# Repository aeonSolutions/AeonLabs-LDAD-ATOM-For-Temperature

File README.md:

[PCB-Prototyping-Catalogue](https://github.com/aeonSolutions/PCB-Prototyping-Catalogue)  >>  [Laboratory Automation](https://github.com/aeonSolutions/PCB-Prototyping-Catalogue/tree/main/Laboratory%20Automation) >>  [Smart DAQs](https://github.com/aeonSolutions/PCB-Prototyping-Catalogue/tree/main/Smart%20DAQ)  >>    [12-bit Smart DAQs](https://github.com/aeonSolutions/PCB-Prototyping-Catalogue/tree/main/Smart%20DAQ/12-bit)  >> LDAD ATOM For Temperature

<br>

#  LDAD ATOM For Temperature
This repo contains the KiCad files for the LDAD ATOM features 1 DS18b20 temperature sensor, has WIFI and BLE connectivity, externally powered 3.3V to 12V such as a USB plug.

LDAD ATOM features 1 I2C (or 1 digital in)  connection, has WIFI and BLE connectivity, externally powered 3.3V to 12V such as a USB plug. This PCB was made to Fit a 45x25mm enclosure.
It can connect 1 digital sensor and up to 8 I2C sensors.

This PCB was made to Fit a [45x25mm](https://s.click.aliexpress.com/e/_A5Elob) enclosure.

*Don't forget to LIKE , SHARE and subscribe the free whatsApp group* and if you liked this PCB consider buying me a cup of coffee. Links below.

### Status
  revision 1.0 tested and working.

If you already tested this PCB send me a message. Thank you

## Revisions
- revision 1.0
  
## Download options
Download this repository if you need the KiCad Files or, download the Gerber files in the release section of this repository

## Liked it ? Get a Free PCB for yourself
Send me your Device or hardware and i will design a custom PCB for it. Free of charge. Contact-me on WhatsApp or email for more info. 

## Q&A WhatsApp Group
If you have any Questions or simply  like this kind of projects and want to stay updated with the latest research ideas and prototypes during the day and week, join the WhatsApp Group
[A.I. Things](https://chat.whatsapp.com/FkNC7u83kuy2QRA5sqjBVg)

## Fully assembled PCB
Alternatively, and if you do not want to build a PCB by yourself and like to buy one:

The price starts at 30eur plus postage fees.
(I will also deliver the assembled PCB with all the components in place at a fair aditonal cost).

#### Be supportive of my dedication and work towards technology education and buy me a coffee. Link below.

________________________________________________________________________________________________________________
## [Go back to main catalogue page](https://github.com/aeonSolutions/PCB-Prototyping-Catalogue)
________________________________________________________________________________________________________________

## PCB Parts list
- DC2DC converter HX4002B x2 : https://s.click.aliexpress.com/e/_Ak7IPx
- Capacitor 100nF SMD 1206 : https://s.click.aliexpress.com/e/_AVdmzr
- Capacitor 2.2uF SMD 1206 : https://s.click.aliexpress.com/e/_AVdmzr
- Resistor SMD 1206 330R x3 : https://s.click.aliexpress.com/e/_A7OXrR
- ESP32 WROOM32 x1 : https://s.click.aliexpress.com/e/_AF7N6l
- KF350 Screw pitch 3.5mm Straight 4 Pin pcb terminal block : https://s.click.aliexpress.com/e/_AChDnp

- This PCB connects with the any I2C compatible sensor such as the SHT3x, SG30, etc :  https://s.click.aliexpress.com/e/_A1piJN

## PCB Enclosure
The enclosure,  a [45x25mm](https://s.click.aliexpress.com/e/_A5Elob) enclosure, for this PCB can be bought online on AliExpress.com

## Firmware Download 
one can use the PCB in the repository [AeonLabs-MCU-Burner-USB-to-UART-TTL](https://github.com/aeonSolutions/AeonLabs-MCU-Burner-USB-to-UART-TTL) to program the ESP32 WROOM32 MCU on this PCB.

______________________________________________________________________________________________________________________________

### License
2022 Creative Commons Attribution-NonCommercial-ShareAlike 4.0 International

https://creativecommons.org/licenses/by-nc-sa/4.0/

### Own a copy of this work
if you like to own a copy of this work, you can buy it as a NFT or Ethereum. contact me for more details at mtpsilva@gmail.com

=====================================================================================
### Share this PCB board files

### Be supportive of my dedication and work towards technology education and buy me a coffee

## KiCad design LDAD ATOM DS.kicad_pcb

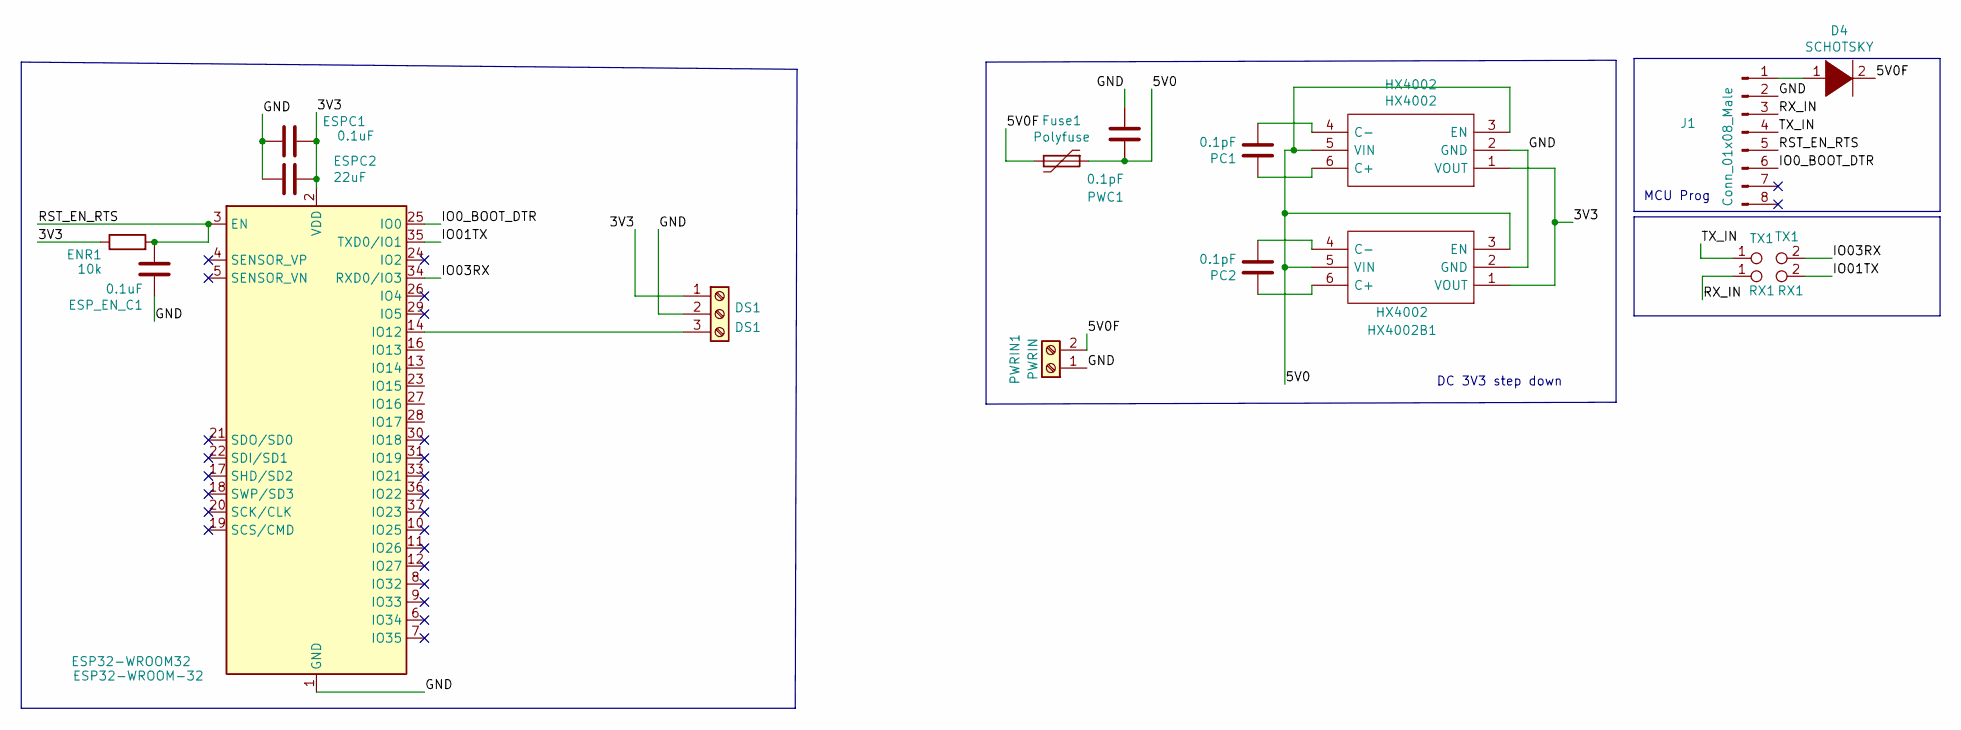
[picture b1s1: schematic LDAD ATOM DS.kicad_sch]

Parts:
D4: SCHOTSKY; D_1210_3225Metric_Pad1.42x2.65mm_HandSolder
DS1: DS1; TerminalBlock_4Ucon_1x03_P3.50mm_Vertical
ENR1: 10k; R_1206_3216Metric_Pad1.30x1.75mm_HandSolder
ESP32-WROOM32: ESP32-WROOM-32
ESPC1: 0.1uF; C_1206_3216Metric_Pad1.33x1.80mm_HandSolder
ESPC2: 22uF; C_1206_3216Metric_Pad1.33x1.80mm_HandSolder
ESP_EN_C1: 0.1uF; C_1206_3216Metric_Pad1.33x1.80mm_HandSolder
Fuse1: Polyfuse; Fuse_1206_3216Metric_Pad1.42x1.75mm_HandSolder
HX4002, HX4002B1: HX4002; HX4002 SOT95 P280X125-6N; Manufacturer_Part_Number HX4002
J1: Conn_01x08_Male; SOIC_clipProgSmall
PC1, PC2: 0.1pF; C_1206_3216Metric_Pad1.33x1.80mm_HandSolder
PWC1: 0.1pF; C_1206_3216Metric_Pad1.33x1.80mm_HandSolder
PWRIN1: PWRIN; TestPoint_2Pads_Pitch2.54mm_Drill0.8mm
RX1: RX1; TestPoint_Pad_Bridge_1.0x1.0mm
TX1: TX1; TestPoint_Pad_Bridge_1.0x1.0mm

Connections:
/3V3: DS1.1, ENR1.1, ESP32-WROOM32.2 (VDD), ESPC1.1, ESPC2.1, HX4002.1 (VOUT), HX4002B1.1 (VOUT)
/5V0: Fuse1.1, HX4002.3 (EN), HX4002.5 (VIN), HX4002B1.3 (EN), HX4002B1.5 (VIN), PWC1.1
/5V0F: D4.2 (A), Fuse1.2, PWRIN1.2
/GND: DS1.2, ESP32-WROOM32.1 (GND), ESP32-WROOM32.15 (GND), ESP32-WROOM32.38 (GND), ESP32-WROOM32.39 (GND), ESPC1.2, ESPC2.2, ESP_EN_C1.1, HX4002.2 (GND), HX4002B1.2 (GND), J1.2, PWC1.2, PWRIN1.1
/IO0_BOOT_DTR: ESP32-WROOM32.25 (IO0), J1.6
/IO01TX: ESP32-WROOM32.35 (TXD0/IO1), RX1.2
/IO03RX: ESP32-WROOM32.34 (RXD0/IO3), TX1.2
/RST_EN_RTS: ENR1.2, ESP32-WROOM32.3 (EN), ESP_EN_C1.2, J1.5
/RX_IN: J1.3, RX1.1
/TX_IN: J1.4, TX1.1
unnamed: DS1.3, ESP32-WROOM32.14 (IO12)
unnamed: HX4002.4 (C-), PC1.2
unnamed: HX4002.6 (C+), PC1.1
unnamed: HX4002B1.4 (C-), PC2.2
unnamed: HX4002B1.6 (C+), PC2.1
unnamed: D4.1 (K), J1.1

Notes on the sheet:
DC 3V3 step down
MCU Prog

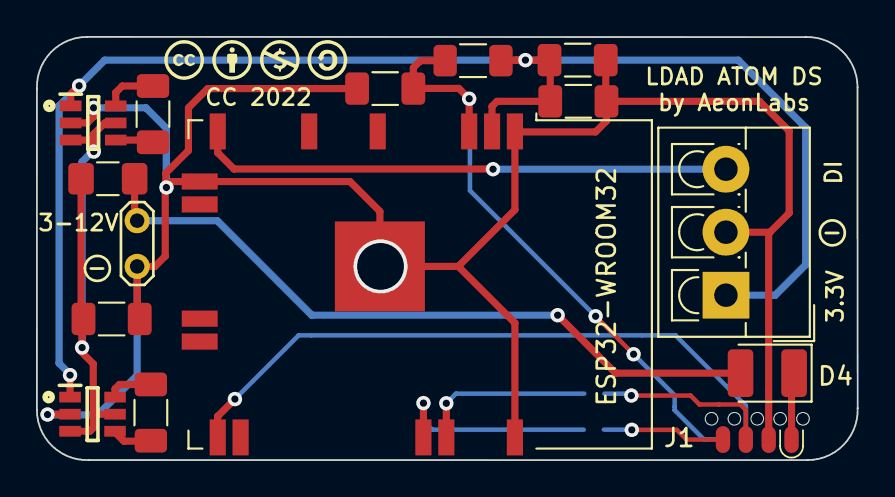
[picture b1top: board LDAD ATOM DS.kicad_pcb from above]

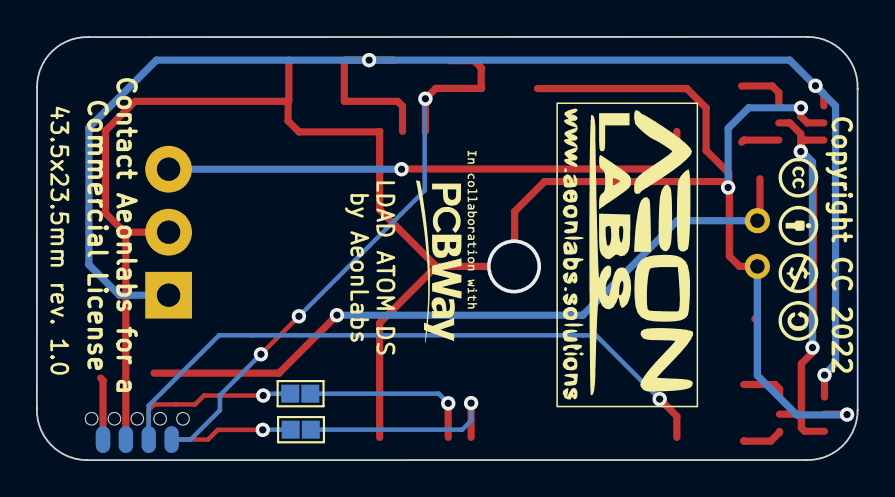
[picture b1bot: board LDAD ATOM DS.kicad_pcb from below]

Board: 2 copper layers, 45.6 x 23.5 mm, 17 parts (2 on the bottom side), 16 nets.

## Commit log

2022-04-24 rev 1.0

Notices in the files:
LDAD ATOM DS.kicad_pcb:
Copyright CC 2022
